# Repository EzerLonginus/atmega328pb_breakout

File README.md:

# atmega328pb_breakout
breakout design for atmega328pb

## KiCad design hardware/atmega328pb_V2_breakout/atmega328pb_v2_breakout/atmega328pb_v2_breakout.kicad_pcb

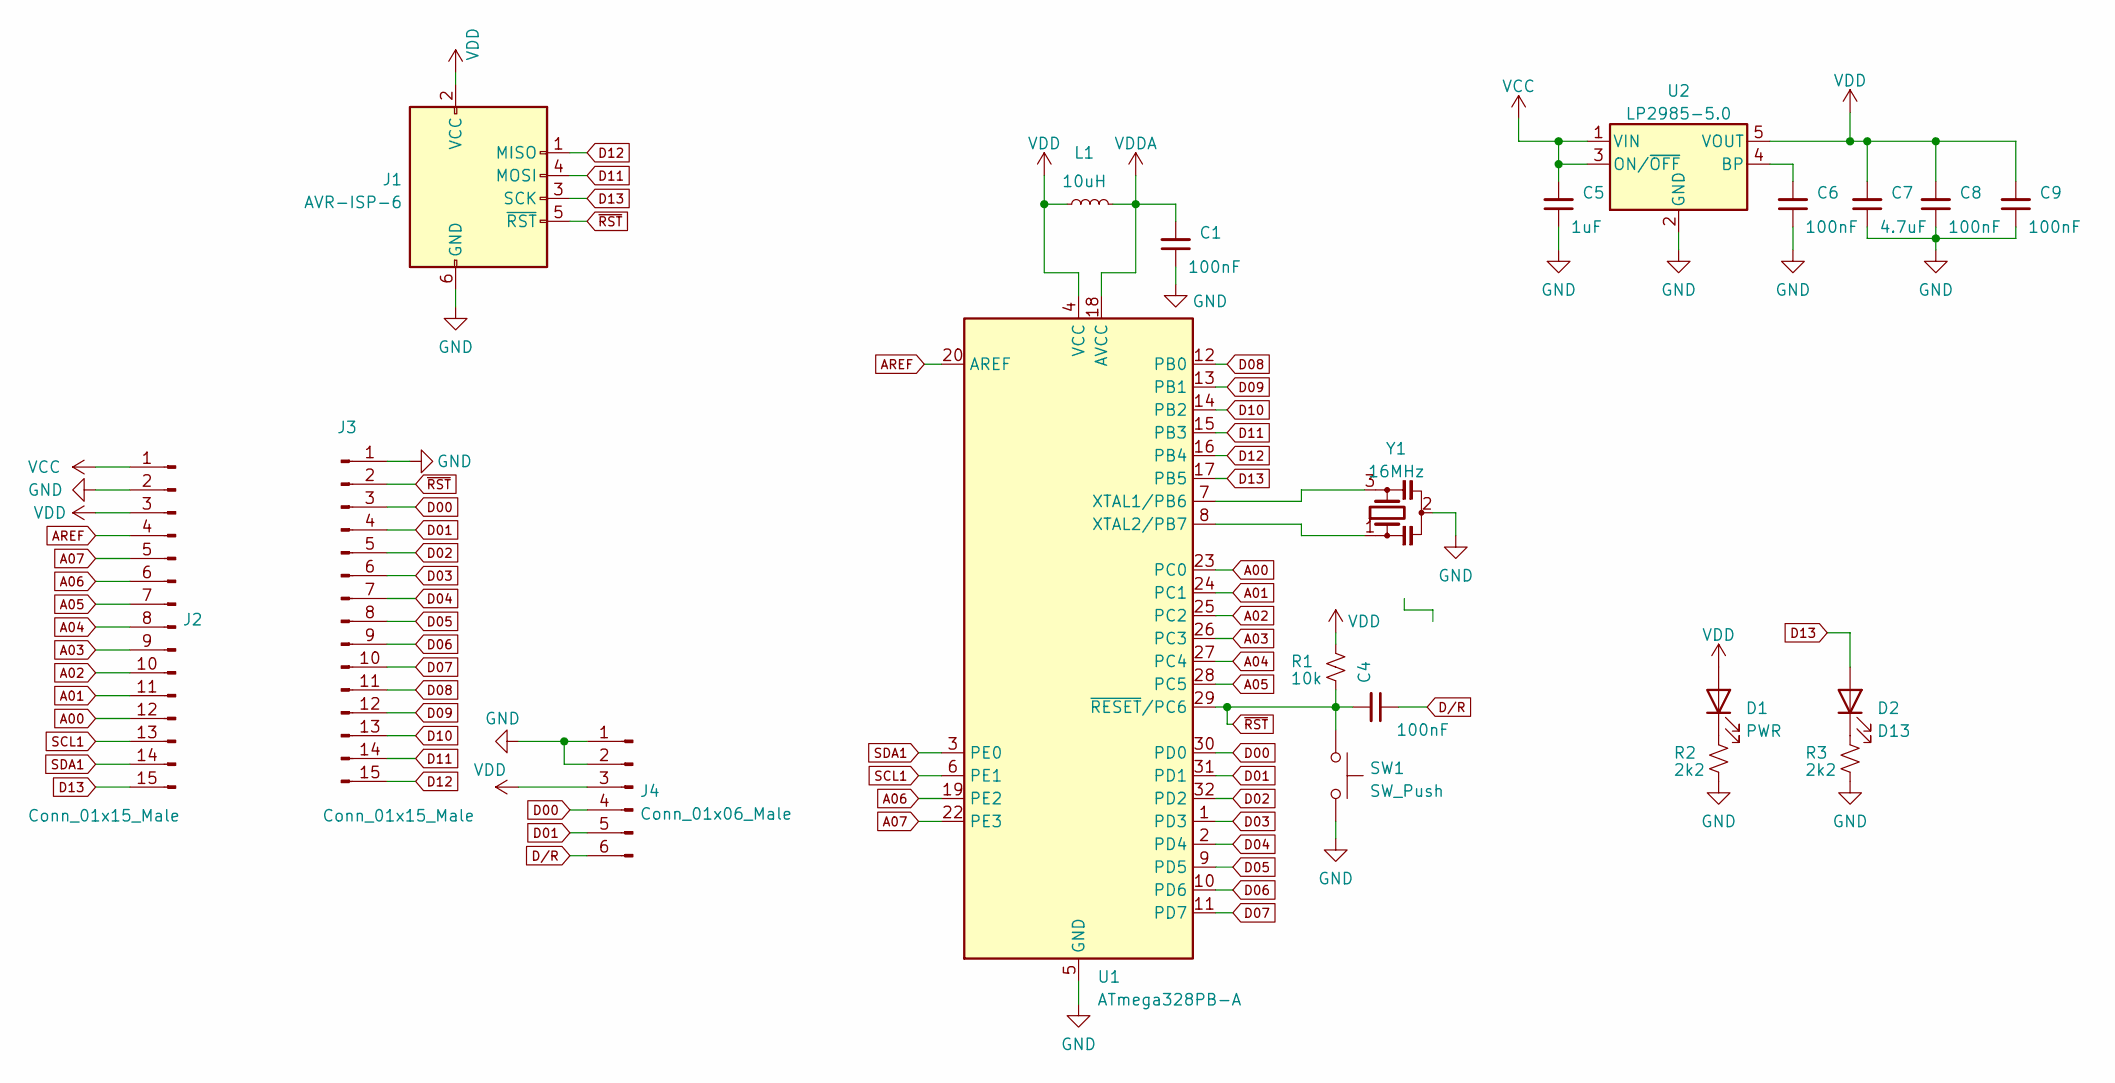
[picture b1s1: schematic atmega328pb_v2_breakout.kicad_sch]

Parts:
C1, C4, C6, C8, C9: 100nF; C_0603_1608Metric_Pad1.08x0.95mm_HandSolder
C5: 1uF; C_0603_1608Metric_Pad1.08x0.95mm_HandSolder
C7: 4.7uF; C_0603_1608Metric_Pad1.08x0.95mm_HandSolder
D1: PWR; LED_0805_2012Metric
D2: D13; LED_0805_2012Metric
J1: AVR-ISP-6; PinHeader_2x03_P2.54mm_Vertical
J2, J3: Conn_01x15_Male; PinHeader_1x15_P2.54mm_Vertical
J4: Conn_01x06_Male; PinHeader_1x06_P2.54mm_Vertical
L1: 10uH; L_0805_2012Metric_Pad1.05x1.20mm_HandSolder
R1: 10k; R_0603_1608Metric_Pad0.98x0.95mm_HandSolder
R2, R3: 2k2; R_0603_1608Metric_Pad0.98x0.95mm_HandSolder
SW1: SW_Push; SW_SPST_B3U-1000P
U1: ATmega328PB-A; TQFP-32_7x7mm_P0.8mm
U2: LP2985-5.0; SOT-23-5
Y1: 16MHz; Resonator_SMD_Murata_CSTxExxV-3Pin_3.0x1.1mm

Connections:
A00: J2.12, U1.23 (PC0)
A01: J2.11, U1.24 (PC1)
A02: J2.10, U1.25 (PC2)
A03: J2.9, U1.26 (PC3)
A04: J2.8, U1.27 (PC4)
A05: J2.7, U1.28 (PC5)
A06: J2.6, U1.19 (PE2)
A07: J2.5, U1.22 (PE3)
AREF: J2.4, U1.20 (AREF)
D00: J3.3, J4.4, U1.30 (PD0)
D01: J3.4, J4.5, U1.31 (PD1)
D02: J3.5, U1.32 (PD2)
D03: J3.6, U1.1 (PD3)
D04: J3.7, U1.2 (PD4)
D05: J3.8, U1.9 (PD5)
D06: J3.9, U1.10 (PD6)
D07: J3.10, U1.11 (PD7)
D08: J3.11, U1.12 (PB0)
D09: J3.12, U1.13 (PB1)
D10: J3.13, U1.14 (PB2)
D11: J1.4 (MOSI), J3.14, U1.15 (PB3)
D12: J1.1 (MISO), J3.15, U1.16 (PB4)
D13: D2.2 (A), J1.3 (SCK), J2.15, U1.17 (PB5)
D/R: C4.1, J4.6
GND: C1.1, C5.1, C6.1, C7.1, C8.1, C9.1, J1.6 (GND), J2.2, J3.1, J4.1, J4.2, R2.2, R3.2, SW1.2, U1.5 (GND), U1.21 (GND), U2.2 (GND), Y1.2
unnamed: C6.2, U2.4 (BP)
unnamed: D1.1 (K), R2.1
unnamed: D2.1 (K), R3.1
unnamed: U1.7 (XTAL1/PB6), Y1.3
unnamed: U1.8 (XTAL2/PB7), Y1.1
SCL1: J2.13, U1.6 (PE1)
SDA1: J2.14, U1.3 (PE0)
VCC: C5.2, J2.1, U2.1 (VIN), U2.3 (ON/~OFF)
VDD: C7.2, C8.2, C9.2, D1.2 (A), J1.2 (VCC), J2.3, J4.3, L1.1, R1.1, U1.4 (VCC), U2.5 (VOUT)
VDDA: C1.2, L1.2, U1.18 (AVCC)
~RST: C4.2, J1.5 (~RST), J3.2, R1.2, SW1.1, U1.29 (~RESET/PC6)

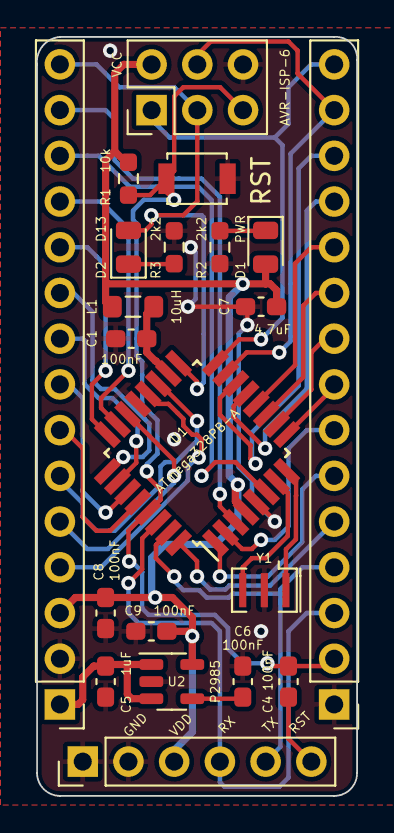
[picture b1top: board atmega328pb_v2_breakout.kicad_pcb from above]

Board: 2 copper layers, 17.8 x 42.2 mm, 21 parts (0 on the bottom side), 36 nets.

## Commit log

2023-07-10 Added slimmer version of breakout
